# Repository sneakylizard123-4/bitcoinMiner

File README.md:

# BitcoinMiner

A single BM1370 board that mines bitcoin

## Custom Features
- BM1370 ASIC miner
- ESP32-S3-WROOM-1/1u-N16R8 MCU for wifi
- 9x WS2812B status LEDs
- Fan controller
- TPS546D24 20A core regulator
- USB-C + TC2030 Tag-Connect

## PCB Design

The board is a 4 layer 100x75mm PCB with a dedicated ground inner layer

It is built around the BM1370 ASIC.
it is based on the proven Bitaxe Gamma reference design, and a buck 20A 1.2V core rail.
The ESP32-S3 module provides WiFi/BLE control. It can be programmed through the native USB-C port or the Tag-Connect debug header
The fan controller communicates to the ESP32 via i2C

## Firmware

The firmware is the open-source
see [firmware/](firmware/). 
To enter program mode:
1. Hold BOOT (SW2)
2. Press RESET (SW1)
3. Release BOOT
4. Start flashing

```
pip install bitaxetool
bitaxetool --config firmware/configs/config-bitcoinMiner.csv --firmware firmware/esp-miner-merged.bin
```

## BOM (Bill of Materials)

| Ref | Value | LCSC # | MPN | Manufacturer | Footprint | Qty | Unit $ | Ext $ | Link |
|-----|-------|--------|-----|--------------|-----------|-----|--------|-------|------|
| C1,C2,C4-C22,C58 | 1uF 16V X7R | C59782 | CL10B105KO8NNNC | Samsung | 0603 | 22 | — | — | [LCSC](https://www.lcsc.com/product-detail/C59782.html) |
| C3,C23-C28,C36,C37 | 0.1uF 16V X7R | C66501 | CL10B104KO8NNNC | Samsung | 0603 | 9 | — | — | [LCSC](https://www.lcsc.com/product-detail/C66501.html) |
| C29,C30,C31,C38,C42,C44 | 1uF 16V X5R | C2177690 | EMK105BJ105MV | Taiyo Yuden | 0402 | 6 | — | — | [LCSC](https://www.lcsc.com/product-detail/C2177690.html) |
| C32,C39 | 10uF 16V X5R | C1713 | CL21A106KOQNNNE | Samsung | 0805 | 2 | — | — | [LCSC](https://www.lcsc.com/product-detail/C1713.html) |
| C33,C45,C48,C59-C67 | 0.1uF 16V X5R | C159816 | CL05A104KO5NNNC | Samsung | 0402 | 12 | — | — | [LCSC](https://www.lcsc.com/product-detail/C159816.html) |
| C34 | 47uF 6.3V X5R | C140782 | GRM188R60J476ME15D | muRata | 0603 | 1 | — | — | [LCSC](https://www.lcsc.com/product-detail/C140782.html) |
| C35 | 470pF 50V C0G | C36252 | 0603CG471J500NT | FH | 0603 | 1 | — | — | [LCSC](https://www.lcsc.com/product-detail/C36252.html) |
| C40,C41 | 47uF 16V X5R | C2932477 | CL32A476KOJNNNE | Samsung | 1210 | 2 | — | — | [LCSC](https://www.lcsc.com/product-detail/C2932477.html) |
| C43 | 4700pF 50V X7R | C599603 | C0402C472K5RAC7867 | KEMET | 0402 | 1 | — | — | [LCSC](https://www.lcsc.com/product-detail/C599603.html) |
| C46 | 2200pF 50V X7R | C106861 | CC0402KRX7R9BB222 | YAGEO | 0402 | 1 | — | — | [LCSC](https://www.lcsc.com/product-detail/C106861.html) |
| C47 | 4.7uF 6.3V X5R | C82453 | GRM155R60J475ME47D | muRata | 0402 | 1 | — | — | [LCSC](https://www.lcsc.com/product-detail/C82453.html) |
| C49 | 1000pF 50V NP0 | C152850 | 0805N102J500CT | Walsin | 0805 | 1 | — | — | [LCSC](https://www.lcsc.com/product-detail/C152850.html) |
| C50 | 100pF 50V C0G | C597014 | 04025A101JAT2A | AVX | 0402 | 1 | — | — | [LCSC](https://www.lcsc.com/product-detail/C597014.html) |
| C51,C52,C53 | 22uF 10V X5R | C441864 | GRM21BR61A226ME44L | muRata | 0805 | 3 | — | — | [LCSC](https://www.lcsc.com/product-detail/C441864.html) |
| C54-C57 | 100uF 6.3V X5R | C15008 | CL31A107MQHNNNE | Samsung | 1206 | 4 | — | — | [LCSC](https://www.lcsc.com/product-detail/C15008.html) |
| D1,D2 | Green LED 0603 | C12624 | KT-0603G | Hubei KENTO | 0603 | 2 | — | — | [LCSC](https://www.lcsc.com/product-detail/C12624.html) |
| D3-D11 | WS2812B-2020 | C965555 | WS2812B-2020 | Worldsemi | PLCC4 2020 | 9 | — | — | [LCSC](https://www.lcsc.com/product-detail/C965555.html) |
| J1 | DC Barrel Jack 2.0x5.5mm | C431534 | 694106106102 | Wuerth | Through Hole | 1 | — | — | [LCSC](https://www.lcsc.com/product-detail/C431534.html) |
| J4 | USB-C Receptacle 16P | C165948 | TYPE-C-31-M-12 | Korean Hroparts Elec | SMD | 1 | — | — | [LCSC](https://www.lcsc.com/product-detail/C165948.html) |
| J6 | Pin Socket 1x4 2.54mm | C2718488 | 2.54-1\*4P | BOOMELE | Through Hole | 1 | — | — | [LCSC](https://www.lcsc.com/product-detail/C2718488.html) |
| J7 | JST SH 4P 1mm | C160390 | BM04B-SRSS-TB(LF)(SN) | JST | SMD | 1 | — | — | [LCSC](https://www.lcsc.com/product-detail/C160390.html) |
| L1 | 300nH Shielded Inductor | — | SLC1175-271MEC | Coilcraft | SMD 11x17mm | 1 | — | — | — |
| R1,R3 | 1K 1% | C22548 | RC0603FR-071KL | YAGEO | 0603 | 2 | — | — | [LCSC](https://www.lcsc.com/product-detail/C22548.html) |
| R13 | 14.7k 1% | C4021671 | CRCW040214K7FKTD | Vishay | 0402 | 1 | — | — | [LCSC](https://www.lcsc.com/product-detail/C4021671.html) |
| R14 | 0 ohm | C881153 | CR0402J0R00Q10Z | Ever Ohms | 0402 | 1 | — | — | [LCSC](https://www.lcsc.com/product-detail/C881153.html) |
| R16 | 3.74k 1% | C2085340 | CRCW04023K74FKED | Vishay | 0402 | 1 | — | — | [LCSC](https://www.lcsc.com/product-detail/C2085340.html) |
| R17 | 11.8k 1% | C324858 | RC-02K1182FT | FH | 0402 | 1 | — | — | [LCSC](https://www.lcsc.com/product-detail/C324858.html) |
| R18 | 68.1k 1% | C844116 | CRCW040268K1FKED | Vishay | 0402 | 1 | — | — | [LCSC](https://www.lcsc.com/product-detail/C844116.html) |
| R19 | 10 1% | C138066 | RC0402FR-0710RL | YAGEO | 0402 | 1 | — | — | [LCSC](https://www.lcsc.com/product-detail/C138066.html) |
| R20 | 1 ohm 0.1% sense | C2912606 | HoAR1206-1/4W-1R-0.1% | Milliohm | 1206 | 1 | — | — | [LCSC](https://www.lcsc.com/product-detail/C2912606.html) |
| R8,R21,R24,R25 | 10k 1% | C98220 | RC0603FR-0710KL | YAGEO | 0603 | 4 | — | — | [LCSC](https://www.lcsc.com/product-detail/C98220.html) |
| R22,R23 | 49.9 1% | C482189 | CRCW040249R9FKED | Vishay | 0402 | 2 | — | — | [LCSC](https://www.lcsc.com/product-detail/C482189.html) |
| R4 | 10k 1% | C60490 | RC0402FR-0710KL | YAGEO | 0402 | 1 | — | — | [LCSC](https://www.lcsc.com/product-detail/C60490.html) |
| R5,R6 | 100 1% | C100700 | CR0603FA1000G | LIZ | 0603 | 2 | — | — | [LCSC](https://www.lcsc.com/product-detail/C100700.html) |
| R7 | 5.6K 1% | C844799 | CRCW06035K60FKEA | Vishay | 0603 | 1 | — | — | [LCSC](https://www.lcsc.com/product-detail/C844799.html) |
| R9 | 8.25k 1% | C185389 | RC0402FR-078K25L | YAGEO | 0402 | 1 | — | — | [LCSC](https://www.lcsc.com/product-detail/C185389.html) |
| SW1,SW2 | Tactile Switch EVQPU | — | EVQPUM02K | PANASONIC | SMD | 2 | — | — | — |
| U10 | ESP32-S3-WROOM-1N16R8 | C2913202 | ESP32-S3-WROOM-1-N16R8 | ESPRESSIF | SMD WROOM | 1 | — | — | [LCSC](https://www.lcsc.com/product-detail/C2913202.html) |
| U11 | EMC2101 | C626968 | EMC2101-R-ACZL-TR | Microchip | TSSOP-8 | 1 | — | — | [LCSC](https://www.lcsc.com/product-detail/C626968.html) |
| U12 | TPS546D24ARVFR | C507280 | TPS546D24ARVFR | TI | LQFN-40 | 1 | — | — | [LCSC](https://www.lcsc.com/product-detail/C507280.html) |
| U2 | 25MHz Crystal | C843258 | NX2016SA-25MHZ-STD-CZS-2 | NDK | 2016-4P | 1 | — | — | [LCSC](https://www.lcsc.com/product-detail/C843258.html) |
| U3 | TLV75712PDBV | C1509296 | TLV75712PDBVR | TI | SOT-23-5 | 1 | — | — | [LCSC](https://www.lcsc.com/product-detail/C1509296.html) |
| U4 | MCP1824T-0802E | C625460 | MCP1824T-0802E/OT | Microchip | SOT-23-5 | 1 | — | — | [LCSC](https://www.lcsc.com/product-detail/C625460.html) |
| U5 | BM1370 | — | BM1370 | Bitmain | LQFP | 1 | — | — | — |
| U6,U7,U8 | SN74LVC1T45DBV | C7843 | SN74LVC1T45DBVR | TI | SOT-23-6 | 3 | — | — | [LCSC](https://www.lcsc.com/product-detail/C7843.html) |
| U9 | TLV75733PDBV | C485517 | TLV75733PDBVR | TI | SOT-23-5 | 1 | — | — | [LCSC](https://www.lcsc.com/product-detail/C485517.html) |
| **Total** | — | — | — | — | — | **116** | — | — | — |

Full CSVs: [LCSC BOM](BOM.csv)
[KiCad generated BOM](kicad/production/bom.csv)
[Pick and place](kicad/production/positions.csv)

## Production

Using JLCPCB
4-Layer
- HASL Lead Free
- 1.6mm thick board

## Credits

- [Bitaxe Gamma](https://github.com/bitaxeorg/BitaxeGamma) - reference schematic and BM1370 support circuitry
- [ESP-Miner](https://github.com/bitaxeorg/ESP-Miner) - firmware this board's target is based on
- [Hack Club](https://hackclub.com/) - funding through Forge

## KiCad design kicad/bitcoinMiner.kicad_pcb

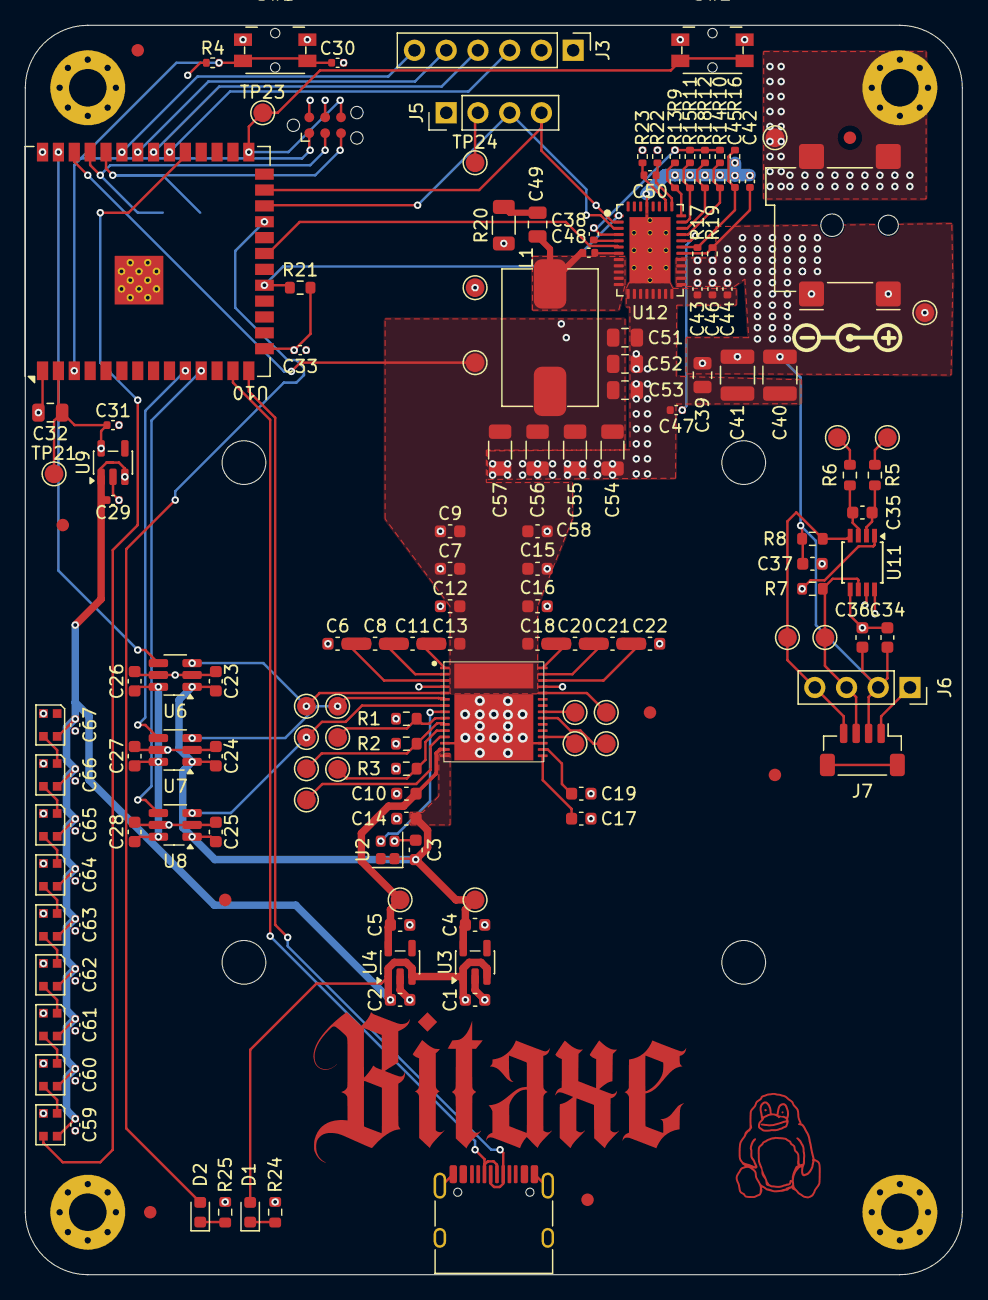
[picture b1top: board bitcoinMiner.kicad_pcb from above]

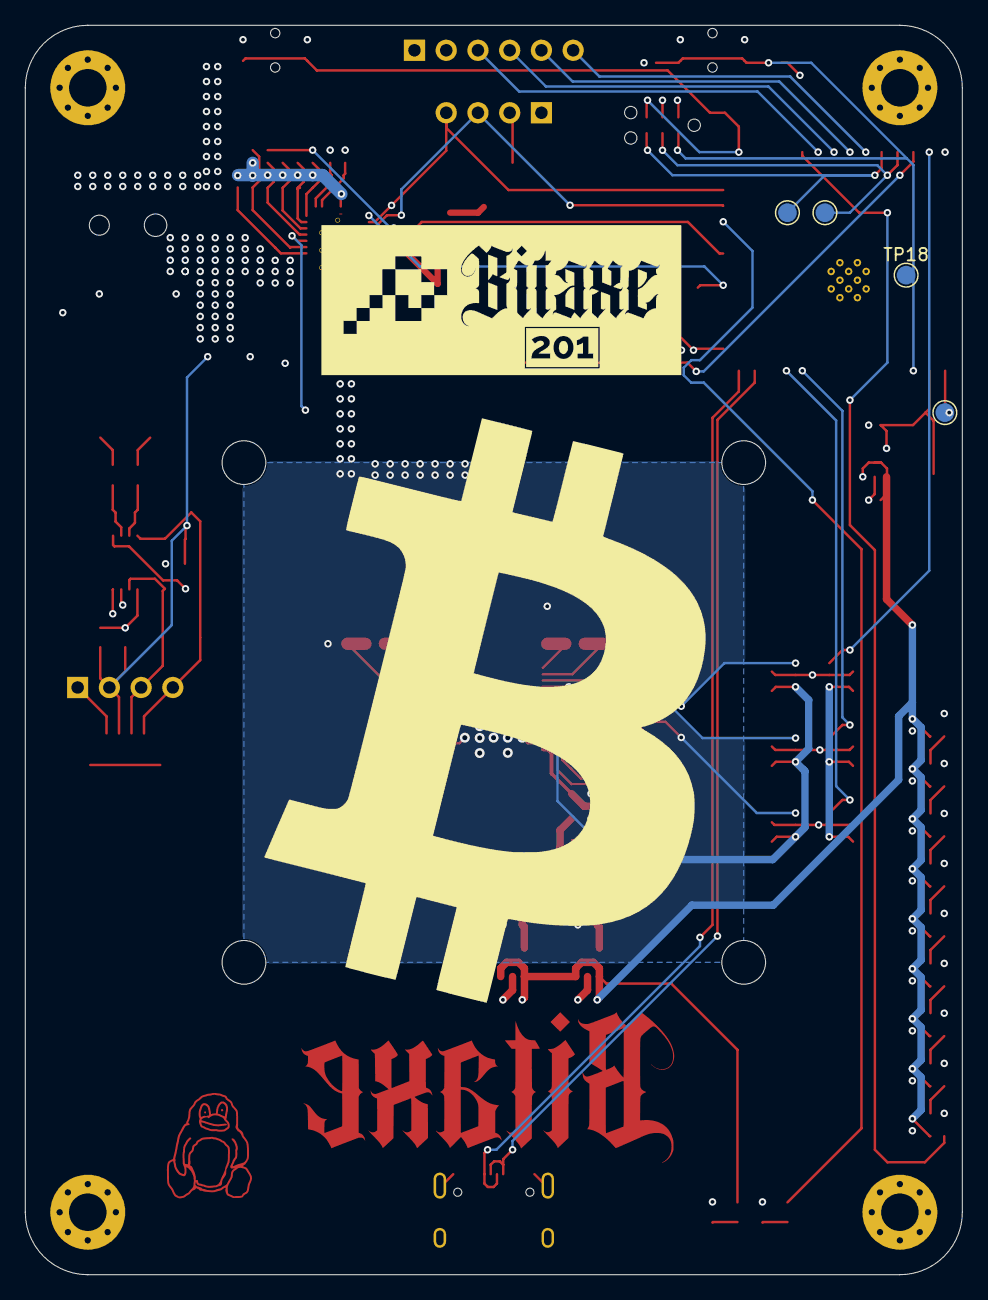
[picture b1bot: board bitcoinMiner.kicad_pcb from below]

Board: 4 copper layers, 75.0 x 100.0 mm, 170 parts (4 on the bottom side), 76 nets.

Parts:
C1, C2, C4, C5, C6, C7, C8, C9, C10, C11, C12, C13, C14, C15, C16, C17, C18, C19, C20, C21, C22, C58: 1uF; C_0603_1608Metric
C3, C23, C24, C25, C26, C27, C28, C36, C37: 0.1uF; C_0603_1608Metric
C29, C30, C31, C38, C42, C44: 1uF; C_0402_1005Metric
C32, C39: 10uF; C_0805_2012Metric
C33, C45, C48, C59, C60, C61, C62, C63, C64, C65, C66, C67: 0.1uF; C_0402_1005Metric
C34: 47uF; C_0603_1608Metric
C35: 470pF; C_0603_1608Metric
C40, C41: 47uF; C_1210_3225Metric
C43: 4700pF; C_0402_1005Metric
C46: 2200pF; C_0402_1005Metric
C47: 4.7uF; C_0402_1005Metric
C49: 1000pF; C_0805_2012Metric
C50: 100pF; C_0402_1005Metric
C51, C52, C53: 22uF; C_0805_2012Metric
C54, C55, C56, C57: 100uF; C_1206_3216Metric
D1, D2: LED; LED_0603_1608Metric
D3, D4, D5, D6, D7, D8, D9, D10, D11: WS2812B-2020; LED_WS2812B-2020_PLCC4_2.0x2.0mm
FID1, FID2, FID3, FID4, FID5, FID6, FID7, FID8: Fiducial; Fiducial_1mm_Mask2mm
H1, H2, H3, H4: MountingHole_Pad; MountingHole_3mm_Pad_Via
H5, H6, H7, H8: MountingHole; MountingHole_3.5mm
J1: 54-00164; BarrelJack_Wuerth_694106106102_2.0x5.5mm
J2: TC2030-IDC; Tag-Connect_TC2030-IDC-NL_2x03_P1.27mm_Vertical
J3: Conn_01x06; PinHeader_1x06_P2.54mm_Vertical
J4: USB_C_Receptacle_USB2.0_14P; USB_C_Receptacle_HRO_TYPE-C-31-M-12
J5: Conn_01x04; PinHeader_1x04_P2.54mm_Vertical
J6: Conn_01x04; PinSocket_1x04_P2.54mm_Vertical
J7: Conn_01x04_MountingPin; JST_SH_BM04B-SRSS-TB_1x04-1MP_P1.00mm_Vertical
L1: 300nH SLC1175-271MEC_COC; L_Coilcraft_SLC1175
R1, R2, R3: 1K; R_0603_1608Metric
R4: 10k; R_0402_1005Metric
R5, R6: 100; R_0603_1608Metric
R7: 5.6K; R_0603_1608Metric
R8: 10K; R_0603_1608Metric
R9: 8.25k; R_0402_1005Metric
R10, R11, R12, R15: R_0402_1005Metric
R13: 14.7k; R_0402_1005Metric
R14: 0; R_0402_1005Metric
R16: 3.74k; R_0402_1005Metric
R17: 11.8k; R_0402_1005Metric
R18: 68.1k; R_0402_1005Metric
R19: 10; R_0402_1005Metric
R20: 1; R_1206_3216Metric
R21, R24, R25: 10k; R_0603_1608Metric
R22, R23: 49.9; R_0402_1005Metric
SW1, SW2: SW_Push; Panasonic_EVQPUM_EVQPUD
T1: net-tie; NetTie-0.25mm
TP1, TP2, TP18, TP19, TP20, TP21, TP22, TP23, TP24, TP29, TP30: TestPoint; TestPoint_Pad_D1.5mm
TP3: 0V8; TestPoint_Pad_D1.5mm
TP4: 1V2; TestPoint_Pad_D1.5mm
TP5: BI; TestPoint_Pad_D1.5mm
TP6: RST_N; TestPoint_Pad_D1.5mm
TP9: ROSC_SEL; TestPoint_Pad_D1.5mm
TP10: LITE_PAD; TestPoint_Pad_D1.5mm
TP11: INV_CLKO; TestPoint_Pad_D1.5mm
TP12: NRSTO; TestPoint_Pad_D1.5mm
TP13: CO; TestPoint_Pad_D1.5mm
TP14: RI; TestPoint_Pad_D1.5mm
TP15: CLKO; TestPoint_Pad_D1.5mm
TP16: BO; TestPoint_Pad_D1.5mm
TP17: PIN_MODE; TestPoint_Pad_D1.5mm
TP25: TEMP_P; TestPoint_Pad_D1.5mm
TP26: TEMP_N; TestPoint_Pad_D1.5mm
TP27: FAN_TACH; TestPoint_Pad_D1.5mm
TP28: FAN_PWM; TestPoint_Pad_D1.5mm
U1: polarity
U2: 25MHz; Crystal_SMD_2016-4Pin_2.0x1.6mm
U3: TLV75712PDBV; SOT-23-5
U4: MCP1824T-0802E; SOT-23-5
U5: BM1370_mode1; BM1370
U6, U7, U8: SN74LVC1T45DBV; SOT-23-6_Handsoldering
U9: TLV75733PDBV; SOT-23-5
U10: ESP32-S3-WROOM-1; ESP32-S3-WROOM-1U
U11: EMC2101; TSSOP-8_3x3mm_P0.65mm
U12: TPS546D24ARVFR; LQFN40-CLIP

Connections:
0V8: C5.1, C10.1, TP3.1 (1_1), U4.5 (VOUT), U5.14 (VDDIO_08_0)
+1V2: C3.1, C4.1, C14.1, C23.1, C24.1, C25.1, TP4.1 (1_1), U2.1 (EN), U2.4 (VIN), U3.5 (OUT), U5.15 (VDDIO_12_0), U6.1 (VCCA), U7.1 (VCCA), U8.1 (VCCA)
+3.3V: C26.1, C27.1, C28.1, C31.1, C32.1, C33.1, J2.2, J5.2, R4.1, R7.2, R21.2, TP21.1 (1_1), TP24.1 (1_1), U6.6 (VCCB), U7.6 (VCCB), U8.6 (VCCB), U9.5 (OUT), U10.2 (3V3), U10.15 (IO3), U11.1 (VDD)
+5V: C1.1, C2.1, C29.1, C34.1, C36.1, C37.1, C39.1, C40.1, C41.1, C43.1, C44.1, C46.1, C59.1, C60.1, C61.1, C62.1, C63.1, C64.1, C65.1, C66.1, C67.1, D1.2 (A), D3.4 (VDD), D4.4 (VDD), D5.4 (VDD), D6.4 (VDD), D7.4 (VDD), D8.4 (VDD), D9.4 (VDD), D10.4 (VDD), D11.4 (VDD), J1.1, J3.1, J6.2, J7.2, R8.1, R17.1, R19.1, TP1.1 (1_1), U3.1 (IN), U3.3 (EN), U4.1 (VIN), U4.3 (EN), U9.1 (IN), U9.3 (EN), U12.21 (PVIN), U12.22 (PVIN), U12.23 (PVIN), U12.24 (PVIN), U12.25 (PVIN)
/ESP32/EN: C30.1, J2.1, R4.2, SW1.2, TP18.1 (1_1), U10.3 (EN)
/ESP32/IO0: J2.6, SW2.2, TP23.1 (1_1), U10.27 (IO0)
/ESP32/P_RX: J2.5, TP20.1 (1_1), U10.36 (RXD0)
/ESP32/P_TX: J2.3, TP19.1 (1_1), U10.37 (TXD0)
/ESP32/USB_D+: J4.A6 (D+), J4.B6 (D+), U10.14 (USB_D+)
/ESP32/USB_D-: J4.A7 (D-), J4.B7 (D-), U10.13 (USB_D-)
/Fan/TEMP_N: R6.1, TP26.1 (1_1)
/Fan/TEMP_P: R5.1, TP25.1 (1_1)
/Power/PGOOD: R21.1, U10.19 (IO11), U12.1 (PGD)
/Power/PMB_ALRT: U10.21 (IO13), U12.6 (SMB_ALRT)
/Power/SW: C48.2, C49.2, L1.1, U12.8 (SW), U12.9 (SW), U12.10 (SW), U12.11 (SW), U12.12 (SW)
/SCL: J5.3, U10.24 (IO47), U11.8 (SMCLK), U12.3 (PMB_CLK)
/SDA: J5.4, U10.25 (IO48), U11.7 (SMDATA), U12.2 (PMB_DATA)
/VDD: C7.2, C9.2, C12.2, C13.2, C15.2, C16.2, C18.1, C51.1, C52.1, C53.1, C54.1, C55.1, C56.1, C57.1, C58.2, L1.2, R22.1, TP29.1 (1_1), U5.31 (VDD), U10.38 (IO2)
BI: R1.2, TP5.1 (1_1), U5.9 (BI)
BO: TP16.1 (1_1), U5.22 (BO)
CI: TP13.1 (1_1), U5.6 (CI), U7.3 (A)
CLKI: U2.3 (OUT), U5.8 (CLKI)
CLKO: TP15.1 (1_1), U5.23 (CLKO)
FAN_PWM: J6.4, J7.4, R8.2, TP28.1 (1_1), U11.4 (FAN)
FAN_TACH: J6.3, J7.3, R7.1, TP27.1 (1_1), U11.6 (ALERT/TACH)
GND: C1.2, C2.2, C3.2, C4.2, C5.2, C6.1, C7.1, C9.1, C10.2, C12.1, C14.2, C15.1, C16.1, C17.2, C19.2, C22.2, C23.2, C24.2, C25.2, C26.2, C27.2, C28.2, C29.2, C30.2, C31.2, C32.2, C33.2, C34.2, C36.2, C37.2, C39.2, C40.2, C41.2, C43.2, C44.2, C46.2, C47.2, C51.2, C52.2, C53.2, C54.2, C55.2, C56.2, C57.2, C58.1, C59.2, C60.2, C61.2, C62.2, C63.2, C64.2, C65.2, C66.2, C67.2, D3.2 (VSS), D4.2 (VSS), D5.2 (VSS), D6.2 (VSS), D7.2 (VSS), D8.2 (VSS), D9.2 (VSS), D10.2 (VSS), D11.2 (VSS), H1.1 (1_1), H2.1 (1_1), H3.1 (1_1), H4.1 (1_1), J1.2, J1.3, J2.4, J3.2, J4.A1 (GND), J4.A12 (GND), J4.B1 (GND), J4.B12 (GND), J4.SH (SHIELD), J5.1, J6.1, J7.1, R1.1, R2.1, R3.1, R20.1, R23.2, R24.2, R25.2, SW1.1, SW2.1, T1.2, TP2.1 (1_1), TP22.1 (1_1), TP30.1 (1_1), U2.2 (GND), U3.2 (GND), U4.2 (GND), U5.4 (VSS), U5.13 (PLL_VSS), U5.18 (VSS), U5.27 (VSS), U5.32 (VSS), U6.2 (GND), U6.5 (DIR), U7.2 (GND), U7.5 (DIR), U8.2 (GND), U8.5 (DIR), U9.2 (GND), U10.1 (GND), U10.40 (GND), U10.41 (GND), U11.5 (GND), U12.13 (PGND), U12.14 (PGND), U12.15 (PGND), U12.16 (PGND), U12.17 (PGND), U12.18 (PGND), U12.19 (PGND), U12.20 (PGND), U12.41 (PAD)
GNDA: C42.1, C45.2, R13.1, R14.2, R15.2, R16.2, R18.2, T1.1, U12.37 (AGND)
NRSTO: TP12.1 (1_1), U5.26 (NRSTO)
unnamed: C49.1, R20.2
unnamed: D1.1 (K), R24.1
unnamed: D2.2 (A), U10.23 (IO21)
unnamed: D2.1 (K), R25.1
unnamed: D3.3 (DIN), U10.31 (IO38)
unnamed: D3.1 (DOUT), D4.3 (DIN)
unnamed: D4.1 (DOUT), D5.3 (DIN)
unnamed: D5.1 (DOUT), D6.3 (DIN)
unnamed: D6.1 (DOUT), D7.3 (DIN)
unnamed: D7.1 (DOUT), D8.3 (DIN)
unnamed: D8.1 (DOUT), D9.3 (DIN)
unnamed: D9.1 (DOUT), D10.3 (DIN)
unnamed: D10.1 (DOUT), D11.3 (DIN)
unnamed: J3.3, U10.32 (IO39)
unnamed: J3.4, U10.33 (IO40)
unnamed: J3.5, U10.34 (IO41)
unnamed: J3.6, U10.35 (IO42)
unnamed: TP11.1 (1_1), U5.12 (INV_CLKO)
unnamed: R3.2, TP10.1 (1_1), U5.11 (LITE_PAD)
unnamed: R2.2, TP9.1 (1_1), U5.10 (ROSC_SEL)
unnamed: C6.2, C8.1, U5.3 (VDD1_0)
unnamed: C21.2, C22.1, U5.28 (VDD1_1)
unnamed: C8.2, C11.1, U5.2 (VDD2_0)
unnamed: C20.2, C21.1, U5.29 (VDD2_1)
unnamed: C11.2, C13.1, U5.1 (VDD3_0)
unnamed: C18.2, C20.1, U5.30 (VDD3_1)
unnamed: C19.1, U5.17 (VDDIO_08_1)
unnamed: C17.1, U5.16 (VDDIO_12_1)
unnamed: R11.2, R15.1, U12.31 (ADRSEL)
unnamed: C42.2, R19.2, U12.26 (AVIN)
unnamed: C48.1, U12.7 (BOOT)
unnamed: C38.2, R9.1, R10.1, R11.1, R12.1, U12.4 (BP1V5)
unnamed: C38.1, U12.5 (DRTN)
unnamed: C45.1, R16.1, R17.2, U12.27 (EN/UVLO)
unnamed: C50.2, R23.1, U12.34 (GOSNS)
unnamed: R9.2, R13.2, U12.32 (MSEL1)
unnamed: R10.2, R14.1, U12.29 (MSEL2)
unnamed: C47.1, U12.28 (VDD5)
unnamed: C50.1, R22.2, U12.33 (VOSNS)
unnamed: R12.2, R18.1, U12.30 (VSEL)
PIN_MODE: TP17.1 (1_1), U5.19 (PIN_MODE)
RO: TP14.1 (1_1), U5.7 (RO), U8.3 (A)
RST: U6.4 (B), U10.39 (IO1)
RST_N: TP6.1 (1_1), U5.5 (NRSTI), U6.3 (A)
RX: U8.4 (B), U10.11 (IO18)
TEMP_DN: C35.2, R6.2, U11.3 (DN)
TEMP_DP: C35.1, R5.2, U11.2 (DP)
TX: U7.4 (B), U10.10 (IO17)

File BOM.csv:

Designator,Footprint,Quantity,Value,LCSC Part #,LCSC Link
"C1, C10, C11, C12, C13, C14, C15, C16, C17, C18, C19, C2, C20, C21, C22, C4, C5, C58, C6, C7, C8, C9",0603,22,1uF,C59782,https://www.lcsc.com/search?q=C59782
"C23, C24, C25, C26, C27, C28, C3, C36, C37",0603,9,0.1uF,C66501,https://www.lcsc.com/search?q=C66501
"C29, C30, C31, C38, C42, C44",0402,6,1uF,C2177690,https://www.lcsc.com/search?q=C2177690
"C32, C39",0805,2,10uF,C1713,https://www.lcsc.com/search?q=C1713
"C33, C45, C48, C59, C60, C61, C62, C63, C64, C65, C66, C67",0402,12,0.1uF,C159816,https://www.lcsc.com/search?q=C159816
C34,0603,1,47uF,C140782,https://www.lcsc.com/search?q=C140782
C35,0603,1,470pF,C36252,https://www.lcsc.com/search?q=C36252
"C40, C41",1210,2,47uF,C2932477,https://www.lcsc.com/search?q=C2932477
C43,0402,1,4700pF,C599603,https://www.lcsc.com/search?q=C599603
C46,0402,1,2200pF,C106861,https://www.lcsc.com/search?q=C106861
C47,0402,1,4.7uF,C82453,https://www.lcsc.com/search?q=C82453
C49,0805,1,1000pF,C152850,https://www.lcsc.com/search?q=C152850
C50,0402,1,100pF,C597014,https://www.lcsc.com/search?q=C597014
"C51, C52, C53",0805,3,22uF,C441864,https://www.lcsc.com/search?q=C441864
"C54, C55, C56, C57",1206,4,100uF,C15008,https://www.lcsc.com/search?q=C15008
"D1, D2",0603,2,LED,C12624,https://www.lcsc.com/search?q=C12624
"D10, D11, D3, D4, D5, D6, D7, D8, D9",LED_WS2812B-2020_PLCC4_2.0x2.0mm,9,WS2812B-2020,C965555,https://www.lcsc.com/search?q=C965555
J1,BarrelJack_Wuerth_694106106102_2.0x5.5mm,1,54-00164,C431534,https://www.lcsc.com/search?q=C431534
J4,USB_C_Receptacle_HRO_TYPE-C-31-M-12,1,USB_C_Receptacle_USB2.0_14P,C165948,https://www.lcsc.com/search?q=C165948
J6,PinSocket_1x04_P2.54mm_Vertical,1,Conn_01x04,C2718488,https://www.lcsc.com/search?q=C2718488
J7,JST_SH_BM04B-SRSS-TB_1x04-1MP_P1.00mm_Vertical,1,Conn_01x04_MountingPin,C160390,https://www.lcsc.com/search?q=C160390
L1,L_Coilcraft_SLC1175,1,300nH SLC1175-271MEC_COC,,"Not on LCSC (Coilcraft) - order SLC1175-271MEC from Coilcraft/Mouser/DigiKey"
"R1, R3",0603,2,1K,C22548,https://www.lcsc.com/search?q=C22548
R13,0402,1,14.7k,C4021671,https://www.lcsc.com/search?q=C4021671
R14,0402,1,0,C881153,https://www.lcsc.com/search?q=C881153
R16,0402,1,3.74k,C2085340,https://www.lcsc.com/search?q=C2085340
R17,0402,1,11.8k,C324858,https://www.lcsc.com/search?q=C324858
R18,0402,1,68.1k,C844116,https://www.lcsc.com/search?q=C844116
R19,0402,1,10,C138066,https://www.lcsc.com/search?q=C138066
R20,1206,1,1,C2912606,https://www.lcsc.com/search?q=C2912606
"R21, R24, R25, R8",0603,4,10k,C98220,https://www.lcsc.com/search?q=C98220
"R22, R23",0402,2,49.9,C482189,https://www.lcsc.com/search?q=C482189
R4,0402,1,10k,C60490,https://www.lcsc.com/search?q=C60490
"R5, R6",0603,2,100,C100700,https://www.lcsc.com/search?q=C100700
R7,0603,1,5.6K,C844799,https://www.lcsc.com/search?q=C844799
R9,0402,1,8.25k,C185389,https://www.lcsc.com/search?q=C185389
"SW1, SW2",Panasonic_EVQPUM_EVQPUD,2,SW_Push,,"Not on LCSC (Panasonic EVQPU series) - order from Mouser/DigiKey"
TP10,TestPoint_Pad_D1.5mm,1,LITE_PAD,,Bare test pad - no part
TP11,TestPoint_Pad_D1.5mm,1,INV_CLKO,,Bare test pad - no part
TP12,TestPoint_Pad_D1.5mm,1,NRSTO,,Bare test pad - no part
TP13,TestPoint_Pad_D1.5mm,1,CO,,Bare test pad - no part
TP14,TestPoint_Pad_D1.5mm,1,RI,,Bare test pad - no part
TP15,TestPoint_Pad_D1.5mm,1,CLKO,,Bare test pad - no part
TP16,TestPoint_Pad_D1.5mm,1,BO,,Bare test pad - no part
TP17,TestPoint_Pad_D1.5mm,1,PIN_MODE,,Bare test pad - no part
TP25,TestPoint_Pad_D1.5mm,1,TEMP_P,,Bare test pad - no part
TP26,TestPoint_Pad_D1.5mm,1,TEMP_N,,Bare test pad - no part
TP27,TestPoint_Pad_D1.5mm,1,FAN_TACH,,Bare test pad - no part
TP28,TestPoint_Pad_D1.5mm,1,FAN_PWM,,Bare test pad - no part
TP3,TestPoint_Pad_D1.5mm,1,0V8,,Bare test pad - no part
TP4,TestPoint_Pad_D1.5mm,1,1V2,,Bare test pad - no part
TP5,TestPoint_Pad_D1.5mm,1,BI,,Bare test pad - no part
TP6,TestPoint_Pad_D1.5mm,1,RST_N,,Bare test pad - no part
TP9,TestPoint_Pad_D1.5mm,1,ROSC_SEL,,Bare test pad - no part
U10,ESP32-S3-WROOM-1U,1,ESP32-S3-WROOM-1,C2913202,https://www.lcsc.com/search?q=C2913202
U11,TSSOP-8_3x3mm_P0.65mm,1,EMC2101,C626968,https://www.lcsc.com/search?q=C626968
U12,LQFN40-CLIP,1,TPS546D24ARVFR,C507280,https://www.lcsc.com/search?q=C507280
U2,Crystal_SMD_2016-4Pin_2.0x1.6mm,1,25MHz,C843258,https://www.lcsc.com/search?q=C843258
U3,SOT-23-5,1,TLV75712PDBV,C1509296,https://www.lcsc.com/search?q=C1509296
U4,SOT-23-5,1,MCP1824T-0802E,C625460,https://www.lcsc.com/search?q=C625460
U5,BM1370,1,BM1370_mode1,,"Not on LCSC (Bitmain ASIC) - source from Bitmain/secondary market"
"U6, U7, U8",SOT-23-6_Handsoldering,3,SN74LVC1T45DBV,C7843,https://www.lcsc.com/search?q=C7843
U9,SOT-23-5,1,TLV75733PDBV,C485517,https://www.lcsc.com/search?q=C485517

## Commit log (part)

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2026-02-14 add readme
2026-02-14 finish copying schematic from bitaxe
2026-02-16 add ethernet sheet
2026-02-16 update other sheets
2026-02-16 update power sheet
2026-02-16 random updates
2026-03-09 update pcb
2026-03-10 clean files
